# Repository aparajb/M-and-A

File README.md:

# M&amp;A
#### M&amp;A Repository
**The Team:** Aparaj Bogahawatta, Matthew Feros, Gus Gannon
---------------------------------------------------------------------------------
**We are an Australian lightweight soccer team, competing in the Robocup Junior Lighweight League, as part of Brisbane Boys' College Robotics.**
For enquiries relating to BBC Robotics please visit:
[Brisbane Boys' College Website](http://www.bbc.qld.edu.au).

Alternatively, please contact the Head of Soccer at BBC: [Steven Lau](mailto:slau2@bbc.qld.edu.au).

For more information about Robocup Australia, please visit: [Robocup Junior Australia](https://www.robocupjunior.org.au/).

For more information about our Robots, please visit our website: [M&amp;A Robotics](https://bbcrobotics-mna.weebly.com).

## Folder Structure
- M&amp;A 2018 : All the designs, electronics and software for our 2018 national robots
    - Hardware : Contains all the structural components and electronic components of our robot
    - Log Book : Contains the manufacturing process of our original robot
    - Management : Contains some files for management
    - Orders : Contains an order spreadsheet which has all our electrical and structural components
    - Software : Contains the software for our microcontrollers
        - lib : Contains libraries of code referred to in the main program
        - src : Contains the source code for the Master Teensy

- M&amp;A 2019 : All the designs, electronics and software for our 2019 international robots
    - Documentation : Contains a handout, presentation and poster for our team.
    - Hardware : Contains all the structural components and electronic components of our robot
    - Orders : Contains an order spreadsheet which has all our electrical and structural components
    - Project Management : Contains our project management plan for the international competition
    - Rules : Contains the international and national rules    
    - Software : Contains the software for our microcontrollers
        - lib : Contains libraries of code referred to in the main program
        - src : Contains the source code for the Master Teensy
        
## Primary Robot Components
- Maxon DCX19s Motors
- Custom Made Omniwheels (3D Print, Laser Cut and CNC)
- Main PCB
    - Teensy 3.5
    - 24 TSSPs
    - IMU (MPU9250)
    - HC-05 Bluetooth Module
    - OpenMV H7
- Light Sensor PCB
    - 32 Light Sensors Arranged in a Circular Formation
- LRF PCB
    - 4 LRFs
- Custom Designed 360° Camera Mirror
## Programming Checklist
- [x] Establish Movement of Motors
- [x] Compass Correction
- [x] Ball Following + Score
- [x] Line Avoidance
- [x] Goal Tracking
- [x] Inter Robot Communication
## 2019 Objectives
#### General Goals
- [x] Increase Attacker accuracy
- [x] Increase Defender accuracy
- [x] Implement Role switching
## Results
#### Brisbane Regional Competition 2018
- 1st Place
#### Queensland State Competition 2018
- 1st Place
#### Australian National Competition Competition 2018
- 2nd Place
#### International Championships 2019
- 1st Place
---------------------------------------------------------------------------------

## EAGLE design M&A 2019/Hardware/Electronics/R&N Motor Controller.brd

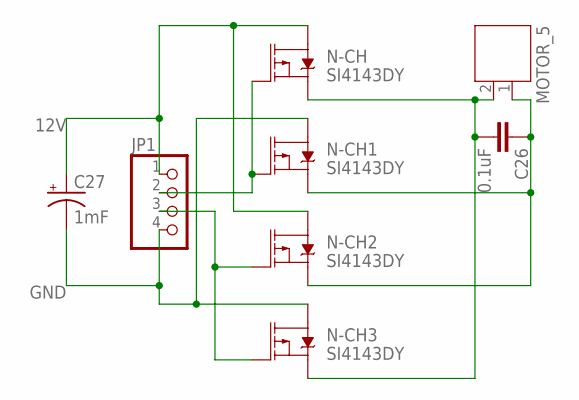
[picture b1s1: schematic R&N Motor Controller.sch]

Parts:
C26: 0.1uF; 0603
C27: 1mF; CPOL-RADIAL-5MM-10MM
JP1: PINHD-1X4; 1X04
MOTOR_5: JST-PH2
N-CH, N-CH1, N-CH2, N-CH3: SI4143DY; SO-8

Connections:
12V: C27.+, JP1.1, N-CH.5 (D), N-CH.6 (D), N-CH.7 (D), N-CH.8 (D), N-CH2.5 (D), N-CH2.6 (D), N-CH2.7 (D), N-CH2.8 (D)
GND: C27.-, JP1.4, N-CH1.5 (D), N-CH1.6 (D), N-CH1.7 (D), N-CH1.8 (D), N-CH3.5 (D), N-CH3.6 (D), N-CH3.7 (D), N-CH3.8 (D)
unnamed: C26.1, MOTOR_5.1, N-CH1.1 (S), N-CH1.2 (S), N-CH1.3 (S), N-CH2.1 (S), N-CH2.2 (S), N-CH2.3 (S)
unnamed: C26.2, MOTOR_5.2, N-CH.1 (S), N-CH.2 (S), N-CH.3 (S), N-CH3.1 (S), N-CH3.2 (S), N-CH3.3 (S)
PWM_INA: JP1.2, N-CH.4 (G), N-CH1.4 (G)
PWM_INB: JP1.3, N-CH2.4 (G), N-CH3.4 (G)

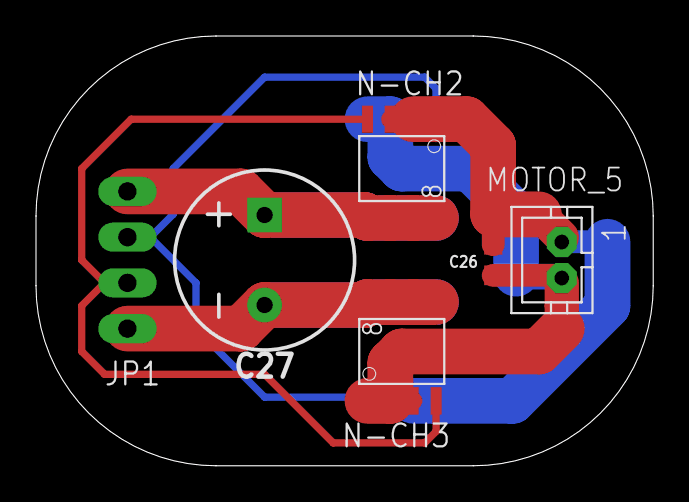
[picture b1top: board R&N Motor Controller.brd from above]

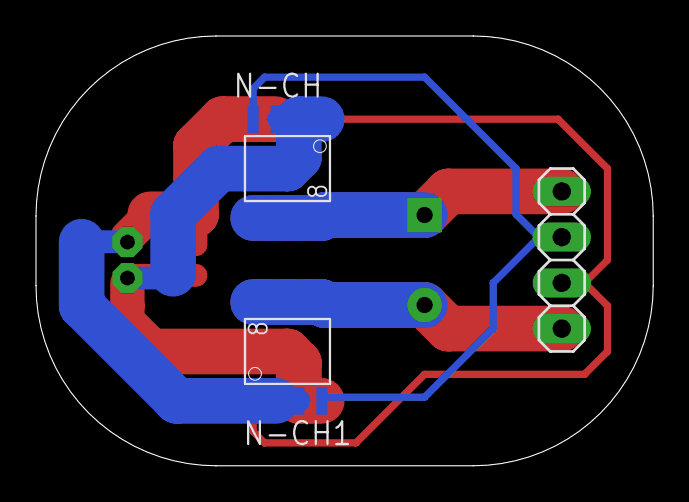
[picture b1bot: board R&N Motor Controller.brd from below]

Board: 2 copper layers, 34.3 x 23.9 mm, 8 parts (3 on the bottom side), 6 nets.

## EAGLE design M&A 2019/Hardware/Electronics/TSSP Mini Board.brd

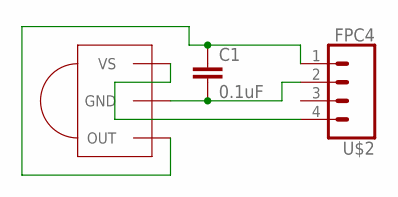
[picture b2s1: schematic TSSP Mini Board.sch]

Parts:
C1: 0.1uF; 0603
U$1: TSSP58038; MINICAST
U$2: FPC4

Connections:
unnamed: C1.1, U$1.1 (OUT), U$2.1
unnamed: C1.2, U$1.2 (GND), U$2.2
unnamed: U$1.3 (VS), U$2.4

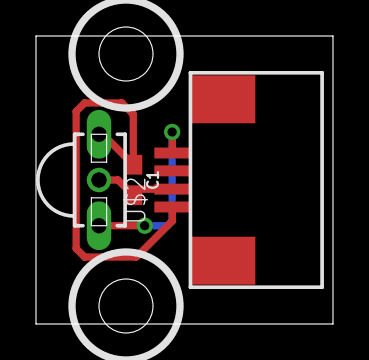
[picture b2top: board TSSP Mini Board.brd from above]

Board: 2 copper layers, 16.5 x 16.0 mm, 3 parts (0 on the bottom side), 3 nets.

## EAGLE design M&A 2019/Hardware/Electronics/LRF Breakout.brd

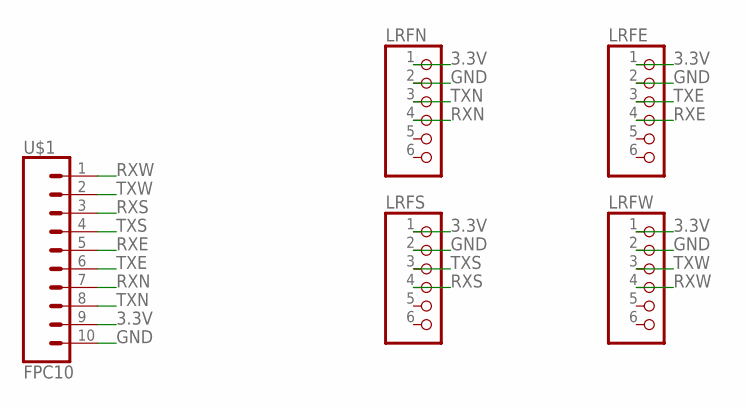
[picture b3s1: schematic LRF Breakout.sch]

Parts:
LRFE: PINHD-1X6; 1X06
LRFN: PINHD-1X6; 1X06
LRFS: PINHD-1X6; 1X06
LRFW: PINHD-1X6; 1X06
U$1: FPC10

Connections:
3.3V: LRFE.1, LRFN.1, LRFS.1, LRFW.1, U$1.9
GND: LRFE.2, LRFN.2, LRFS.2, LRFW.2, U$1.10
RXE: LRFE.4, U$1.5
RXN: LRFN.4, U$1.7
RXS: LRFS.4, U$1.3
RXW: LRFW.4, U$1.1
TXE: LRFE.3, U$1.6
TXN: LRFN.3, U$1.8
TXS: LRFS.3, U$1.4
TXW: LRFW.3, U$1.2

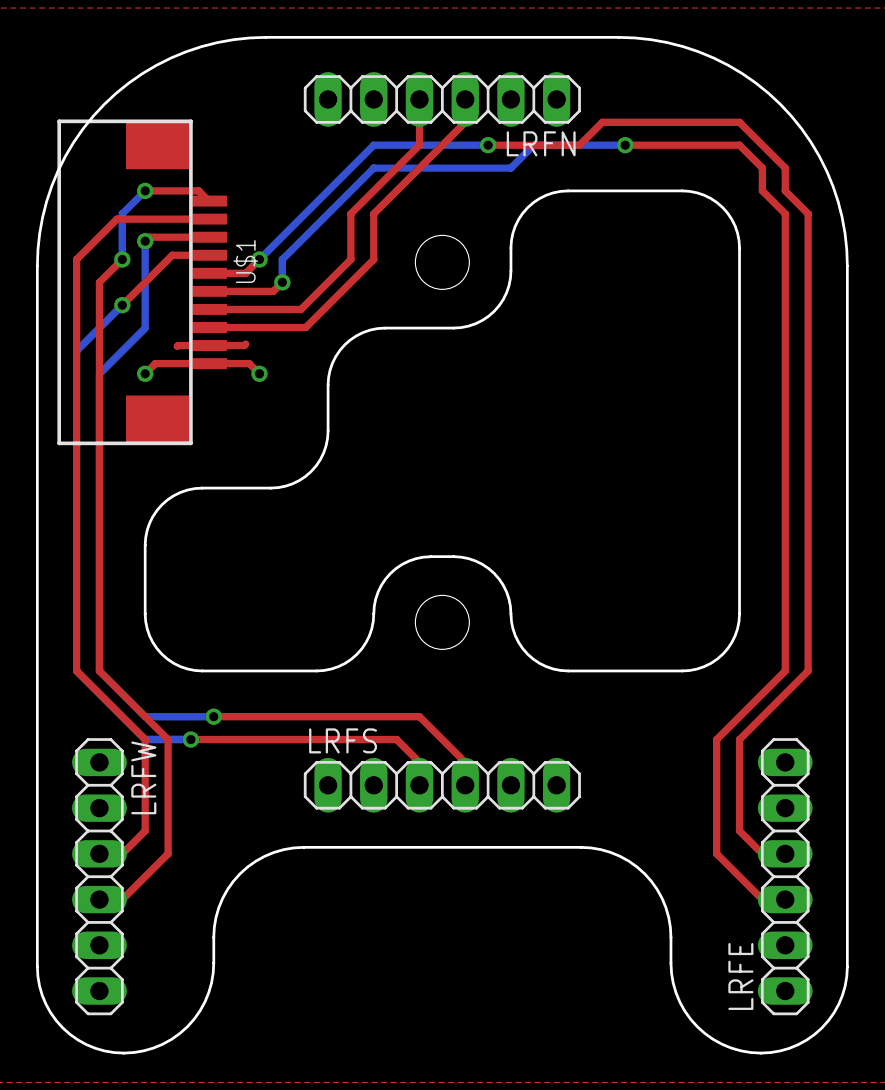
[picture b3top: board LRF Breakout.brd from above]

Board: 2 copper layers, 45.0 x 56.4 mm, 5 parts (0 on the bottom side), 10 nets.

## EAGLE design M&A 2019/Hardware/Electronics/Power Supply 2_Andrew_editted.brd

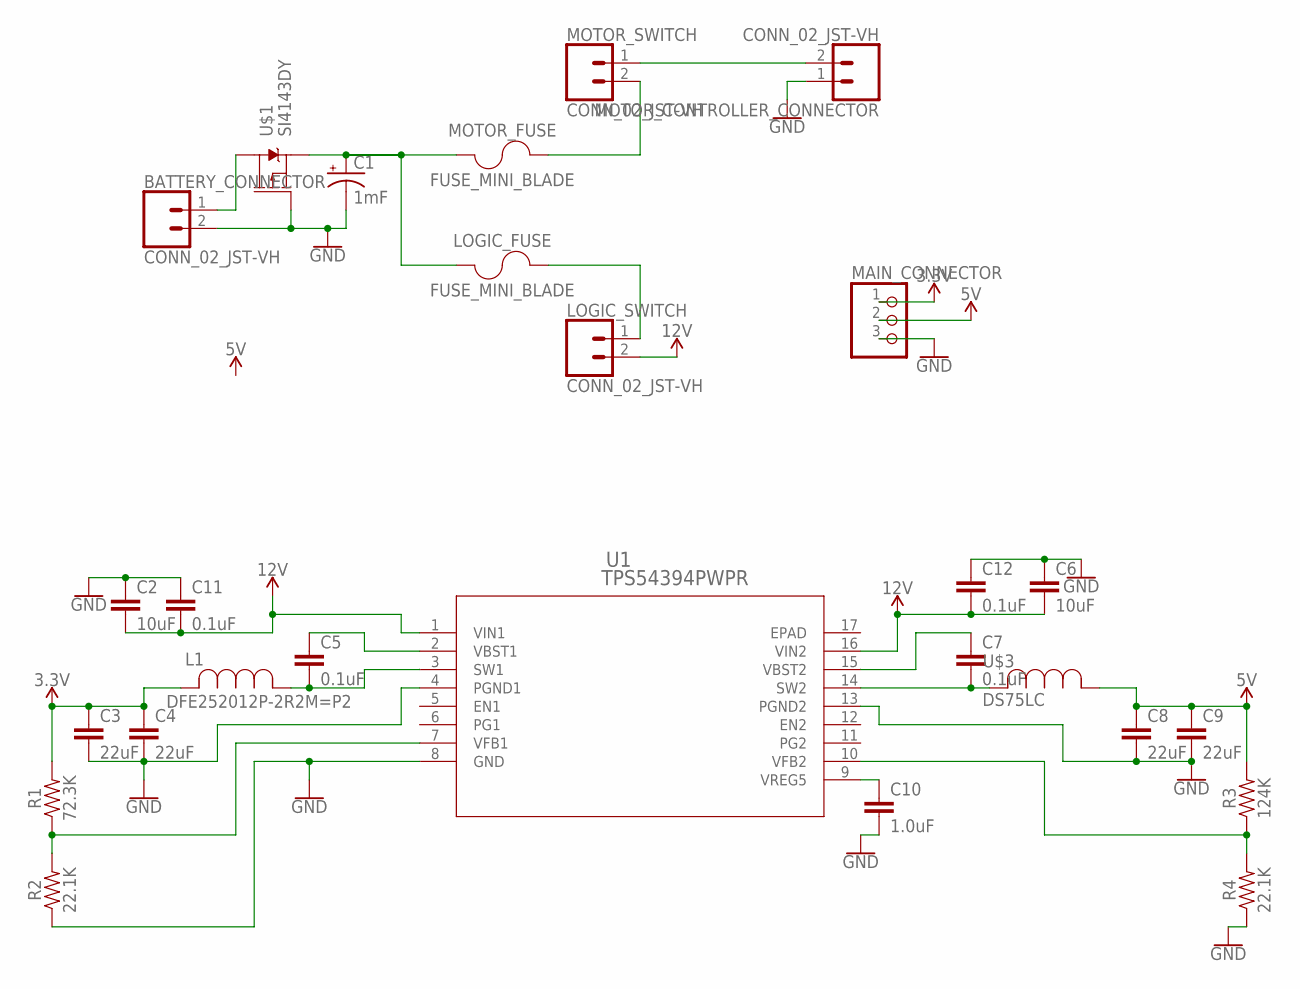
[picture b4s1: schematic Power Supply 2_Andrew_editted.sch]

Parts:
BATTERY_CONNECTOR: CONN_02_JST-VH; B2P-VH
C1: 1mF; CPOL-RADIAL-5MM-10MM
C2, C6: 10uF; 0805
C3, C4, C8, C9: 22uF; 0805
C5, C7, C11, C12: 0.1uF; 0603
C10: 1.0uF; 0805
L1: DFE252012P-2R2M=P2; DFE252012P-1R0M=P2
LOGIC_FUSE: FUSE_MINI_BLADE; SL-1538
LOGIC_SWITCH: CONN_02_JST-VH; B2P-VH
MAIN_CONNECTOR: PINHD-1X3; 1X03
MOTOR_CONTROLLER_CONNECTOR: CONN_02_JST-VH; B2P-VH
MOTOR_FUSE: FUSE_MINI_BLADE; SL-1538
MOTOR_SWITCH: CONN_02_JST-VH; B2P-VH
R1: 72.3K; 0603
R2, R4: 22.1K; 0603
R3: 124K; 0603
U1: TPS54394PWPR; PWP16_3P4X2P46
U$1: SI4143DY; SO-8
U$3: DS75LC

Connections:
3.3V: C3.1, C4.1, L1.2, MAIN_CONNECTOR.1, R1.2
5V: C8.1, C9.1, MAIN_CONNECTOR.2, R3.2, U$3.P$1 (1)
12V: C2.2, C6.2, C11.2, C12.2, LOGIC_SWITCH.2, U1.1 (VIN1), U1.16 (VIN2)
GND: BATTERY_CONNECTOR.2, C1.-, C2.1, C3.2, C4.2, C6.1, C8.2, C9.2, C10.2, C11.1, C12.1, MAIN_CONNECTOR.3, MOTOR_CONTROLLER_CONNECTOR.1, R2.1, R4.1, U1.4 (PGND1), U1.8 (GND), U1.13 (PGND2), U$1.4 (G)
unnamed: BATTERY_CONNECTOR.1, U$1.5 (D), U$1.6 (D), U$1.7 (D), U$1.8 (D)
unnamed: MOTOR_FUSE.P$2 (2), MOTOR_SWITCH.2
unnamed: C1.+, LOGIC_FUSE.P$1 (1), MOTOR_FUSE.P$1 (1), U$1.1 (S), U$1.2 (S), U$1.3 (S)
unnamed: LOGIC_FUSE.P$2 (2), LOGIC_SWITCH.1
unnamed: MOTOR_CONTROLLER_CONNECTOR.2, MOTOR_SWITCH.1
unnamed: C5.1, U1.2 (VBST1)
unnamed: C5.2, L1.1, U1.3 (SW1)
unnamed: C7.1, U1.15 (VBST2)
unnamed: R1.1, R2.2, U1.7 (VFB1)
unnamed: C7.2, U1.14 (SW2), U$3.P$2 (2)
unnamed: C10.1, U1.9 (VREG5)
unnamed: R3.1, R4.2, U1.10 (VFB2)

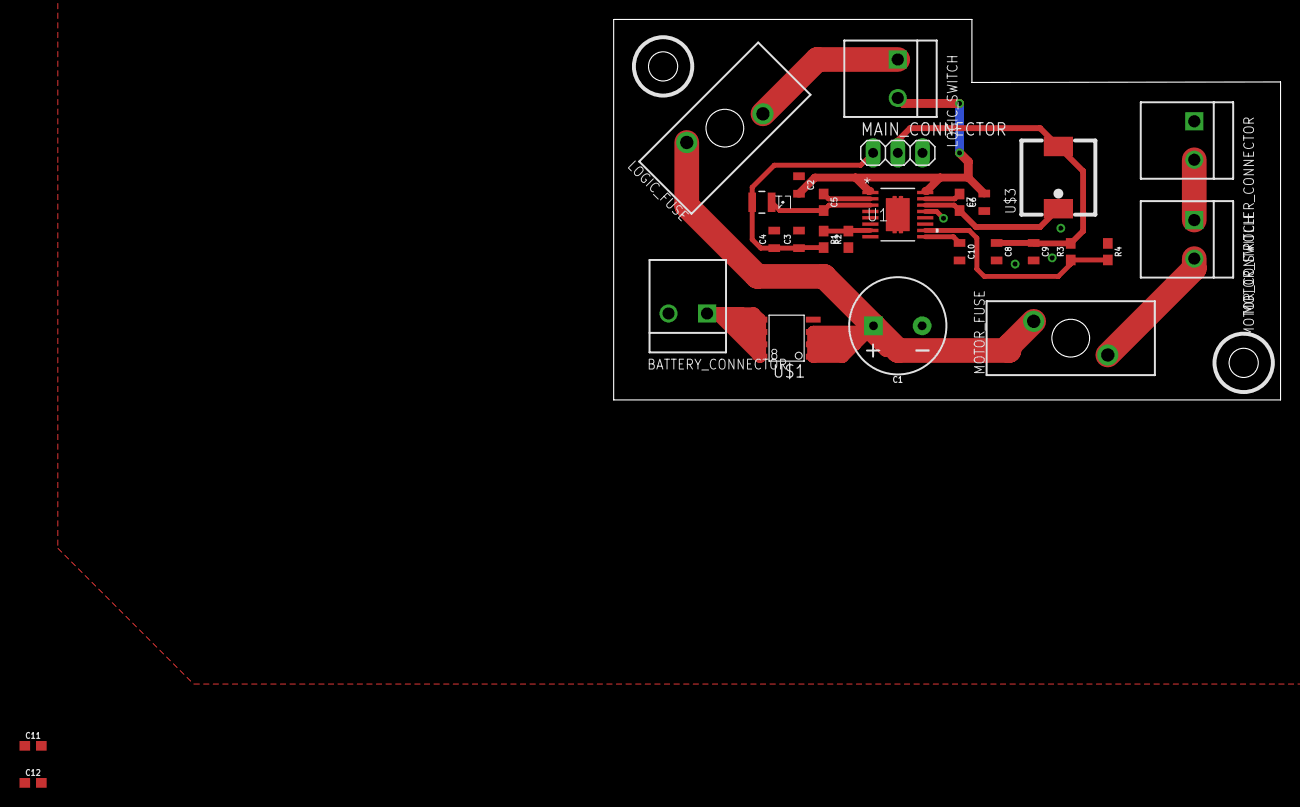
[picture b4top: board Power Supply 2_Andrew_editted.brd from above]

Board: 2 copper layers, 68.6 x 39.1 mm, 27 parts (0 on the bottom side), 16 nets.

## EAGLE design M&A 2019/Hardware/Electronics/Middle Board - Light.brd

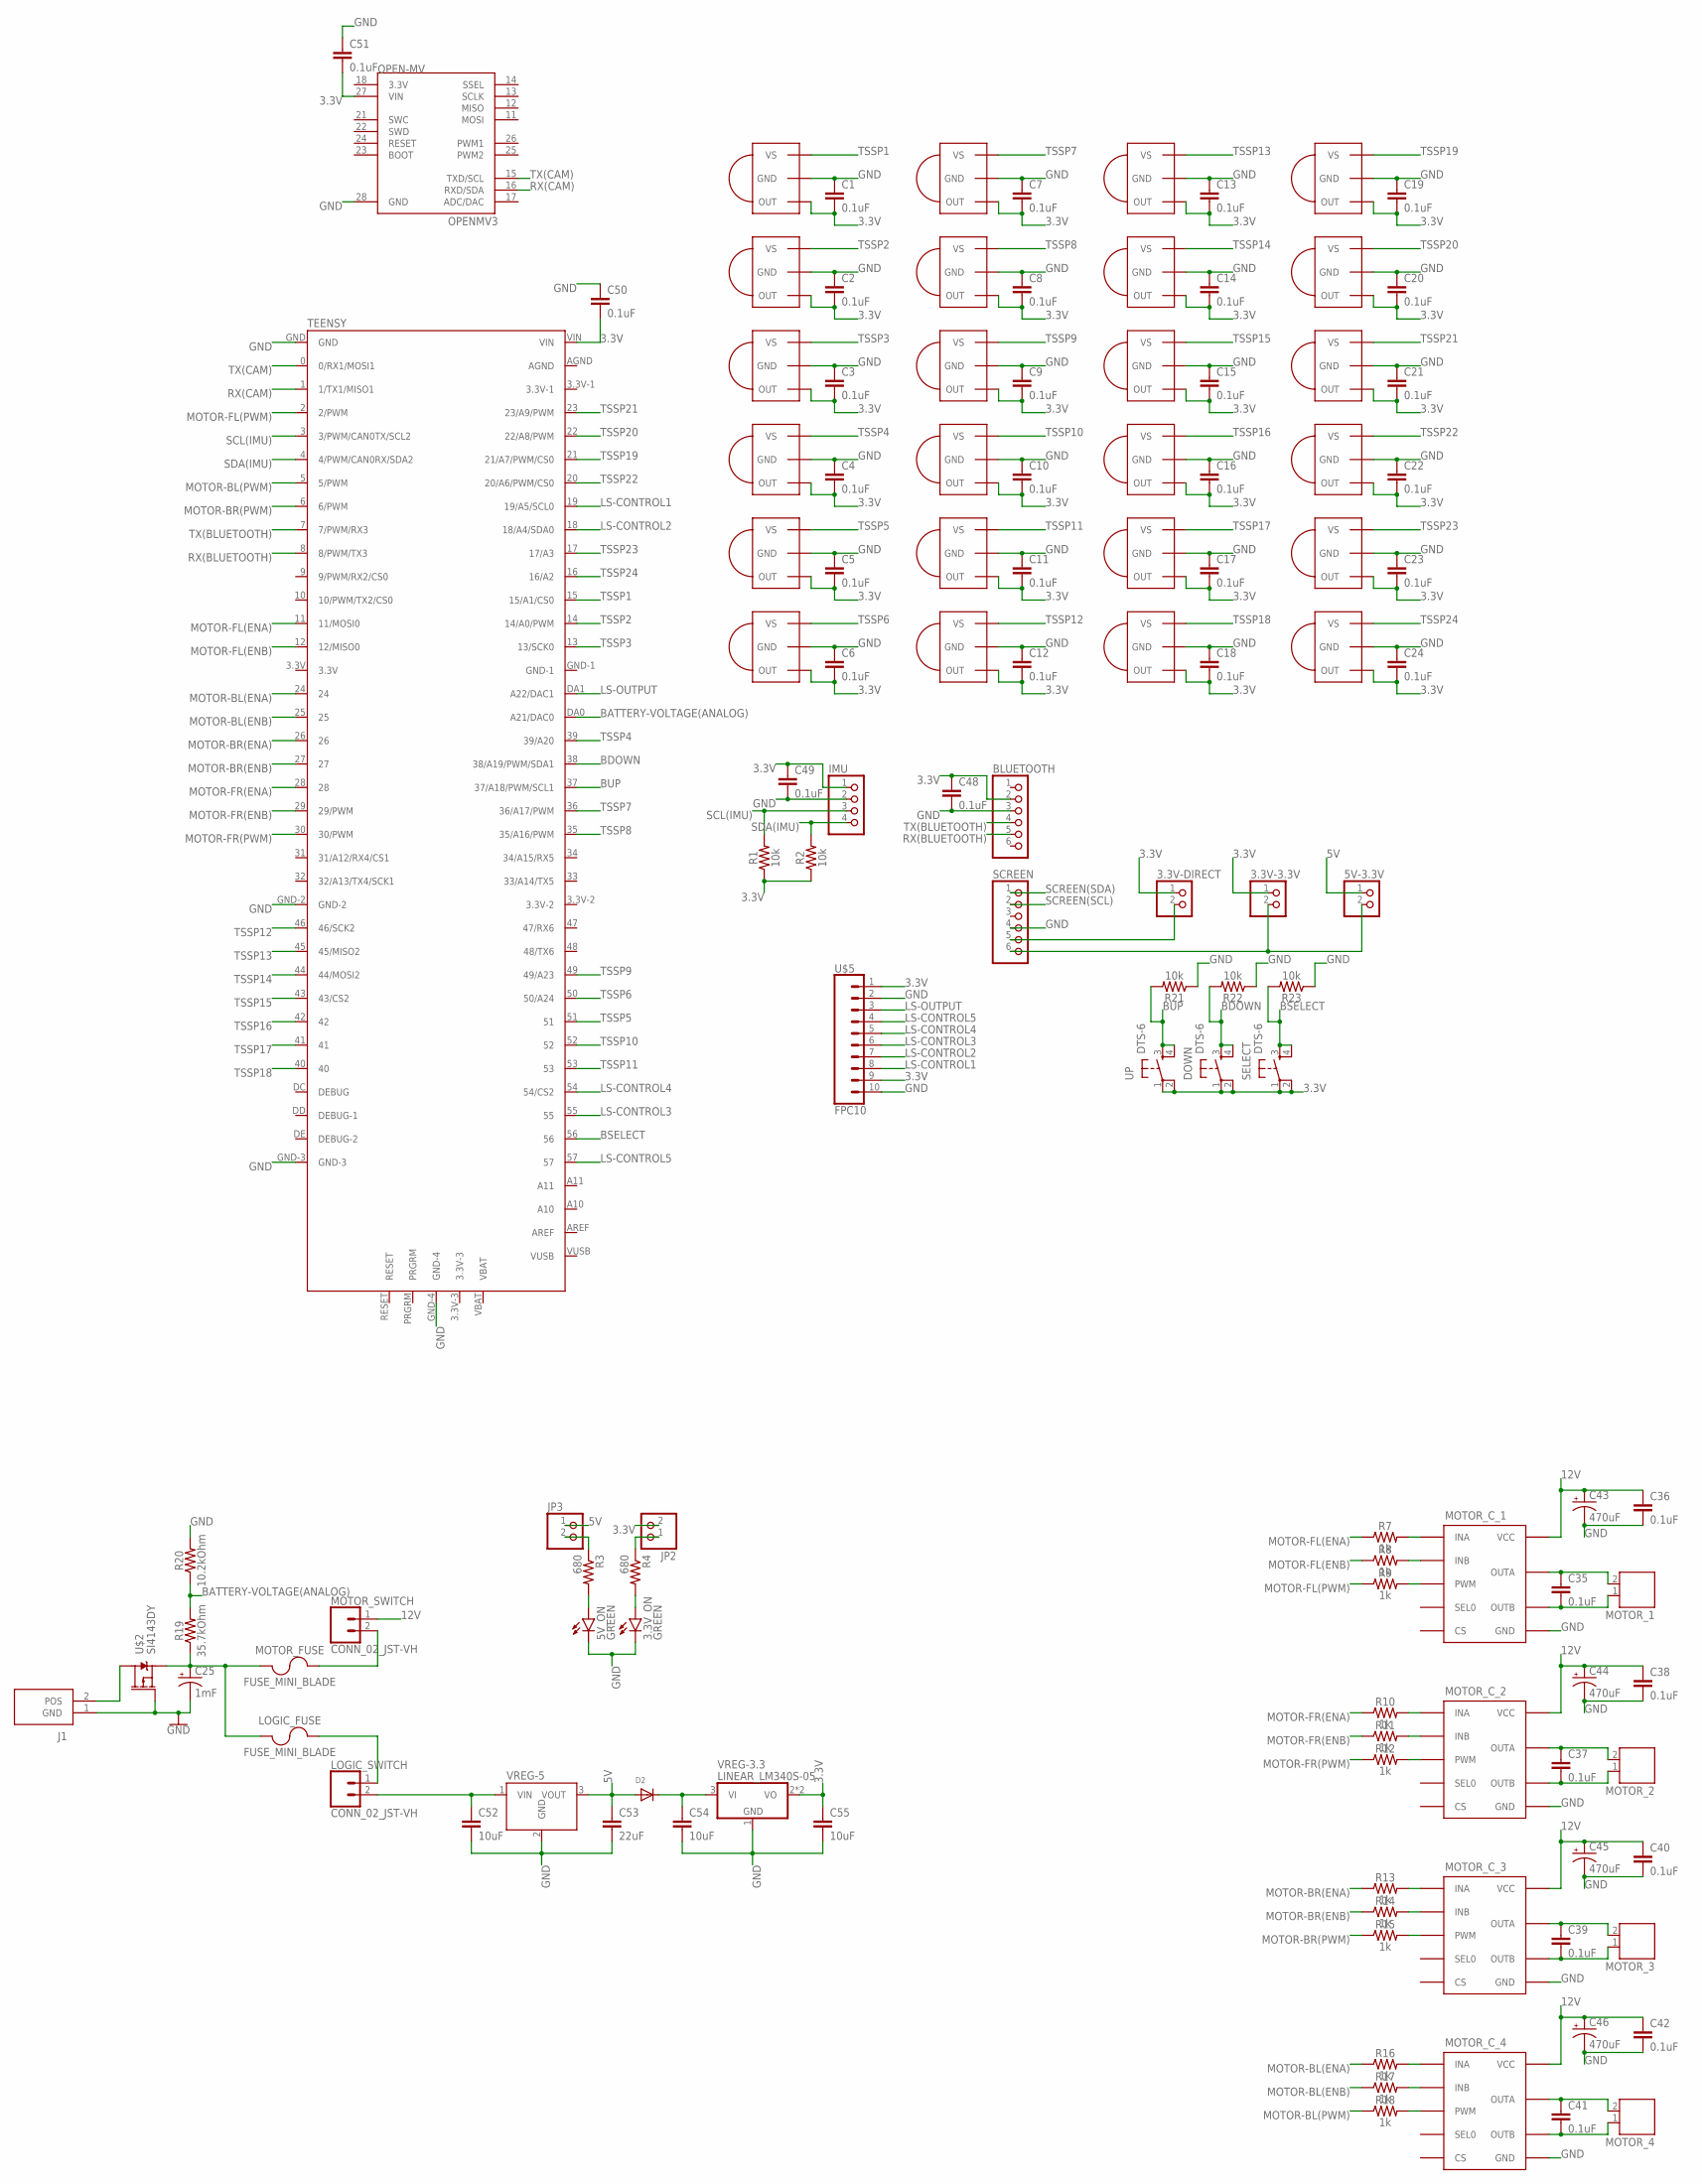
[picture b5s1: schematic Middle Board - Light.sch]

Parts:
3.3V-3.3V, 3.3V-DIRECT, 5V-3.3V: PINHD-1X2; 1X02
3.3V_ON, 5V_ON: GREEN; LED-0603
BLUETOOTH: PINHD-1X6; 1X06
C1, C2, C3, C4, C5, C6, C7, C8, C9, C10, C11, C12, C13, C14, C15, C16, C17, C18, C19, C20, C21, C22, C23, C24, C35, C36, C37, C38, C39, C40, C41, C42, C48, C49, C50, C51: 0.1uF; 0603
C25: 1mF; CPOL-RADIAL-5MM-10MM
C43, C44, C45, C46: 470uF; E3,5-8
C52, C54, C55: 10uF; SPARKFUN-CAPACITORS_0805
C53: 22uF; SPARKFUN-CAPACITORS_1206
D2: ADAFRUIT_DIODE_SOD-123FL:1; ADAFRUIT_SOD-123FL
DOWN: DTS-6
IMU: PINHD-1X4; 1X04
J1: PRT-10474; SHDR2W320P716_1X2_1574X813X158
JP2, JP3: PINHD-1X2/90; 1X02/90
LOGIC_FUSE: FUSE_MINI_BLADE; SL-1538
LOGIC_SWITCH: CONN_02_JST-VH; B2P-VH
MOTOR_1, MOTOR_2, MOTOR_3, MOTOR_4: JST-PH2
MOTOR_C_1, MOTOR_C_2, MOTOR_C_3, MOTOR_C_4: VNH7100BASTR; SO-16
MOTOR_FUSE: FUSE_MINI_BLADE; SL-1538
MOTOR_SWITCH: CONN_02_JST-VH; B2P-VH
OPEN-MV: OPENMV3
R1, R2, R21, R22, R23: 10k; 0603
R3, R4: 680; 0603
R7, R8, R9, R10, R11, R12, R13, R14, R15, R16, R17, R18: 1k; 0603
R19: 35.7kOhm; 0603
R20: 10.2kOhm; 0603
SCREEN: PINHD-1X6; 1X06
SELECT: DTS-6
TEENSY: TEENSY-3.5
TSSP1, TSSP2, TSSP3, TSSP4, TSSP5, TSSP6, TSSP7, TSSP8, TSSP9, TSSP10, TSSP11, TSSP12, TSSP13, TSSP14, TSSP15, TSSP16, TSSP17, TSSP18, TSSP19, TSSP20, TSSP21, TSSP22, TSSP23, TSSP24: TSSP58038; MINICAST
U$2: SI4143DY; SO-8
U$5: FPC10
UP: DTS-6
VREG-3.3: LINEAR_LM340S-05; LINEAR_TO263-3
VREG-5: V78-2000-SWITCHING-REGULATOR_V78-2000

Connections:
3.3V: 3.3V-3.3V.1, 3.3V-DIRECT.1, BLUETOOTH.2, C1.2, C2.2, C3.2, C4.2, C5.2, C6.2, C7.2, C8.2, C9.2, C10.2, C11.2, C12.2, C13.2, C14.2, C15.2, C16.2, C17.2, C18.2, C19.2, C20.2, C21.2, C22.2, C23.2, C24.2, C48.1, C49.1, C50.2, C51.2, C55.1, DOWN.1, DOWN.2, IMU.1, JP2.2, OPEN-MV.27 (VIN), R1.1, R2.1, SELECT.1, SELECT.2, TEENSY.VIN, TSSP1.1 (OUT), TSSP2.1 (OUT), TSSP3.1 (OUT), TSSP4.1 (OUT), TSSP5.1 (OUT), TSSP6.1 (OUT), TSSP7.1 (OUT), TSSP8.1 (OUT), TSSP9.1 (OUT), TSSP10.1 (OUT), TSSP11.1 (OUT), TSSP12.1 (OUT), TSSP13.1 (OUT), TSSP14.1 (OUT), TSSP15.1 (OUT), TSSP16.1 (OUT), TSSP17.1 (OUT), TSSP18.1 (OUT), TSSP19.1 (OUT), TSSP20.1 (OUT), TSSP21.1 (OUT), TSSP22.1 (OUT), TSSP23.1 (OUT), TSSP24.1 (OUT), U$5.1, U$5.9, UP.1, UP.2, VREG-3.3.2 (VO), VREG-3.3.TAB (VO)
3.3V_ON: JP2.1, R4.1
5V: 5V-3.3V.1, C53.1, D2.A, JP3.1, VREG-5.3 (VOUT)
5V-ON: JP3.2, R3.1
12V: C36.1, C38.1, C40.1, C42.1, C43.+, C44.+, C45.+, C46.+, MOTOR_C_1.4 (VCC), MOTOR_C_1.5 (VCC), MOTOR_C_1.12 (VCC), MOTOR_C_2.4 (VCC), MOTOR_C_2.5 (VCC), MOTOR_C_2.12 (VCC), MOTOR_C_3.4 (VCC), MOTOR_C_3.5 (VCC), MOTOR_C_3.12 (VCC), MOTOR_C_4.4 (VCC), MOTOR_C_4.5 (VCC), MOTOR_C_4.12 (VCC), MOTOR_SWITCH.1
BATTERY-VOLTAGE(ANALOG): R19.2, R20.1, TEENSY.DA0 (A21/DAC0)
BDOWN: DOWN.3, DOWN.4, R22.2, TEENSY.38 (38/A19/PWM/SDA1)
BSELECT: R23.2, SELECT.3, SELECT.4, TEENSY.56
BUP: R21.2, TEENSY.37 (37/A18/PWM/SCL1), UP.3, UP.4
GND: 3.3V_ON.C, 5V_ON.C, BLUETOOTH.3, C1.1, C2.1, C3.1, C4.1, C5.1, C6.1, C7.1, C8.1, C9.1, C10.1, C11.1, C12.1, C13.1, C14.1, C15.1, C16.1, C17.1, C18.1, C19.1, C20.1, C21.1, C22.1, C23.1, C24.1, C25.-, C36.2, C38.2, C40.2, C42.2, C43.-, C44.-, C45.-, C46.-, C48.2, C49.2, C50.1, C51.1, C52.2, C53.2, C54.2, C55.2, IMU.2, J1.1 (GND), MOTOR_C_1.1 (GND), MOTOR_C_1.8 (GND), MOTOR_C_1.9 (GND), MOTOR_C_1.16 (GND), MOTOR_C_2.1 (GND), MOTOR_C_2.8 (GND), MOTOR_C_2.9 (GND), MOTOR_C_2.16 (GND), MOTOR_C_3.1 (GND), MOTOR_C_3.8 (GND), MOTOR_C_3.9 (GND), MOTOR_C_3.16 (GND), MOTOR_C_4.1 (GND), MOTOR_C_4.8 (GND), MOTOR_C_4.9 (GND), MOTOR_C_4.16 (GND), OPEN-MV.28 (GND), R20.2, R21.1, R22.1, R23.1, SCREEN.4, TEENSY.GND, TEENSY.GND-2, TEENSY.GND-3, TEENSY.GND-4, TSSP1.2 (GND), TSSP2.2 (GND), TSSP3.2 (GND), TSSP4.2 (GND), TSSP5.2 (GND), TSSP6.2 (GND), TSSP7.2 (GND), TSSP8.2 (GND), TSSP9.2 (GND), TSSP10.2 (GND), TSSP11.2 (GND), TSSP12.2 (GND), TSSP13.2 (GND), TSSP14.2 (GND), TSSP15.2 (GND), TSSP16.2 (GND), TSSP17.2 (GND), TSSP18.2 (GND), TSSP19.2 (GND), TSSP20.2 (GND), TSSP21.2 (GND), TSSP22.2 (GND), TSSP23.2 (GND), TSSP24.2 (GND), U$2.4 (G), U$5.2, U$5.10, VREG-3.3.1 (GND), VREG-5.2 (GND)
LS-CONTROL1: TEENSY.19 (19/A5/SCL0), U$5.8
LS-CONTROL2: TEENSY.18 (18/A4/SDA0), U$5.7
LS-CONTROL3: TEENSY.55, U$5.6
LS-CONTROL4: TEENSY.54 (54/CS2), U$5.5
LS-CONTROL5: TEENSY.57, U$5.4
LS-OUTPUT: TEENSY.DA1 (A22/DAC1), U$5.3
MOTOR-BL(ENA): R16.1, TEENSY.24
MOTOR-BL(ENB): R17.1, TEENSY.25
MOTOR-BL(PWM): R18.1, TEENSY.5 (5/PWM)
MOTOR-BR(ENA): R13.1, TEENSY.26
MOTOR-BR(ENB): R14.1, TEENSY.27
MOTOR-BR(PWM): R15.1, TEENSY.6 (6/PWM)
MOTOR-FL(ENA): R7.1, TEENSY.11 (11/MOSI0)
MOTOR-FL(ENB): R8.1, TEENSY.12 (12/MISO0)
MOTOR-FL(PWM): R9.1, TEENSY.2 (2/PWM)
MOTOR-FR(ENA): R10.1, TEENSY.28
MOTOR-FR(ENB): R11.1, TEENSY.29 (29/PWM)
MOTOR-FR(PWM): R12.1, TEENSY.30 (30/PWM)
unnamed: J1.2 (POS), U$2.5 (D), U$2.6 (D), U$2.7 (D), U$2.8 (D)
unnamed: MOTOR_FUSE.P$2 (2), MOTOR_SWITCH.2
unnamed: C25.+, LOGIC_FUSE.P$1 (1), MOTOR_FUSE.P$1 (1), R19.1, U$2.1 (S), U$2.2 (S), U$2.3 (S)
unnamed: LOGIC_FUSE.P$2 (2), LOGIC_SWITCH.1
unnamed: MOTOR_C_1.3 (INA), R7.2
unnamed: 5V_ON.A, R3.2
unnamed: 3.3V_ON.A, R4.2
unnamed: MOTOR_C_1.6 (INB), R8.2
unnamed: MOTOR_C_1.11 (PWM), R9.2
unnamed: C35.1, MOTOR_1.2, MOTOR_C_1.2 (OUTA), MOTOR_C_1.15 (OUTA)
unnamed: C35.2, MOTOR_1.1, MOTOR_C_1.7 (OUTB), MOTOR_C_1.10 (OUTB)
unnamed: MOTOR_C_2.3 (INA), R10.2
unnamed: MOTOR_C_2.6 (INB), R11.2
unnamed: MOTOR_C_2.11 (PWM), R12.2
unnamed: C37.1, MOTOR_2.2, MOTOR_C_2.2 (OUTA), MOTOR_C_2.15 (OUTA)
unnamed: C37.2, MOTOR_2.1, MOTOR_C_2.7 (OUTB), MOTOR_C_2.10 (OUTB)
unnamed: MOTOR_C_3.3 (INA), R13.2
unnamed: MOTOR_C_3.6 (INB), R14.2
unnamed: MOTOR_C_3.11 (PWM), R15.2
unnamed: C39.1, MOTOR_3.2, MOTOR_C_3.2 (OUTA), MOTOR_C_3.15 (OUTA)
unnamed: C39.2, MOTOR_3.1, MOTOR_C_3.7 (OUTB), MOTOR_C_3.10 (OUTB)
unnamed: MOTOR_C_4.3 (INA), R16.2
unnamed: MOTOR_C_4.6 (INB), R17.2
unnamed: MOTOR_C_4.11 (PWM), R18.2
unnamed: C41.1, MOTOR_4.2, MOTOR_C_4.2 (OUTA), MOTOR_C_4.15 (OUTA)
unnamed: C41.2, MOTOR_4.1, MOTOR_C_4.7 (OUTB), MOTOR_C_4.10 (OUTB)
unnamed: 3.3V-DIRECT.2, SCREEN.5
unnamed: 3.3V-3.3V.2, 5V-3.3V.2, SCREEN.6
unnamed: C52.1, LOGIC_SWITCH.2, VREG-5.1 (VIN)
unnamed: C54.1, D2.C, VREG-3.3.3 (VI)
RX(BLUETOOTH): BLUETOOTH.5, TEENSY.8 (8/PWM/TX3)
RX(CAM): OPEN-MV.16 (RXD/SDA), TEENSY.1 (1/TX1/MISO1)
SCL(IMU): IMU.3, R1.2, TEENSY.3 (3/PWM/CAN0TX/SCL2)
SCREEN(SCL): SCREEN.2
SCREEN(SDA): SCREEN.1
SDA(IMU): IMU.4, R2.2, TEENSY.4 (4/PWM/CAN0RX/SDA2)
TSSP1: TEENSY.15 (15/A1/CS0), TSSP1.3 (VS)
TSSP2: TEENSY.14 (14/A0/PWM), TSSP2.3 (VS)
TSSP3: TEENSY.13 (13/SCK0), TSSP3.3 (VS)
TSSP4: TEENSY.39 (39/A20), TSSP4.3 (VS)
TSSP5: TEENSY.51, TSSP5.3 (VS)
TSSP6: TEENSY.50 (50/A24), TSSP6.3 (VS)
TSSP7: TEENSY.36 (36/A17/PWM), TSSP7.3 (VS)
TSSP8: TEENSY.35 (35/A16/PWM), TSSP8.3 (VS)
TSSP9: TEENSY.49 (49/A23), TSSP9.3 (VS)
TSSP10: TEENSY.52, TSSP10.3 (VS)
TSSP11: TEENSY.53, TSSP11.3 (VS)
TSSP12: TEENSY.46 (46/SCK2), TSSP12.3 (VS)
TSSP13: TEENSY.45 (45/MISO2), TSSP13.3 (VS)
TSSP14: TEENSY.44 (44/MOSI2), TSSP14.3 (VS)
TSSP15: TEENSY.43 (43/CS2), TSSP15.3 (VS)
TSSP16: TEENSY.42, TSSP16.3 (VS)
TSSP17: TEENSY.41, TSSP17.3 (VS)
TSSP18: TEENSY.40, TSSP18.3 (VS)
TSSP19: TEENSY.21 (21/A7/PWM/CS0), TSSP19.3 (VS)
TSSP20: TEENSY.22 (22/A8/PWM), TSSP20.3 (VS)
TSSP21: TEENSY.23 (23/A9/PWM), TSSP21.3 (VS)
TSSP22: TEENSY.20 (20/A6/PWM/CS0), TSSP22.3 (VS)
TSSP23: TEENSY.17 (17/A3), TSSP23.3 (VS)
TSSP24: TEENSY.16 (16/A2), TSSP24.3 (VS)
TX(BLUETOOTH): BLUETOOTH.4, TEENSY.7 (7/PWM/RX3)
TX(CAM): OPEN-MV.15 (TXD/SCL), TEENSY.0 (0/RX1/MOSI1)

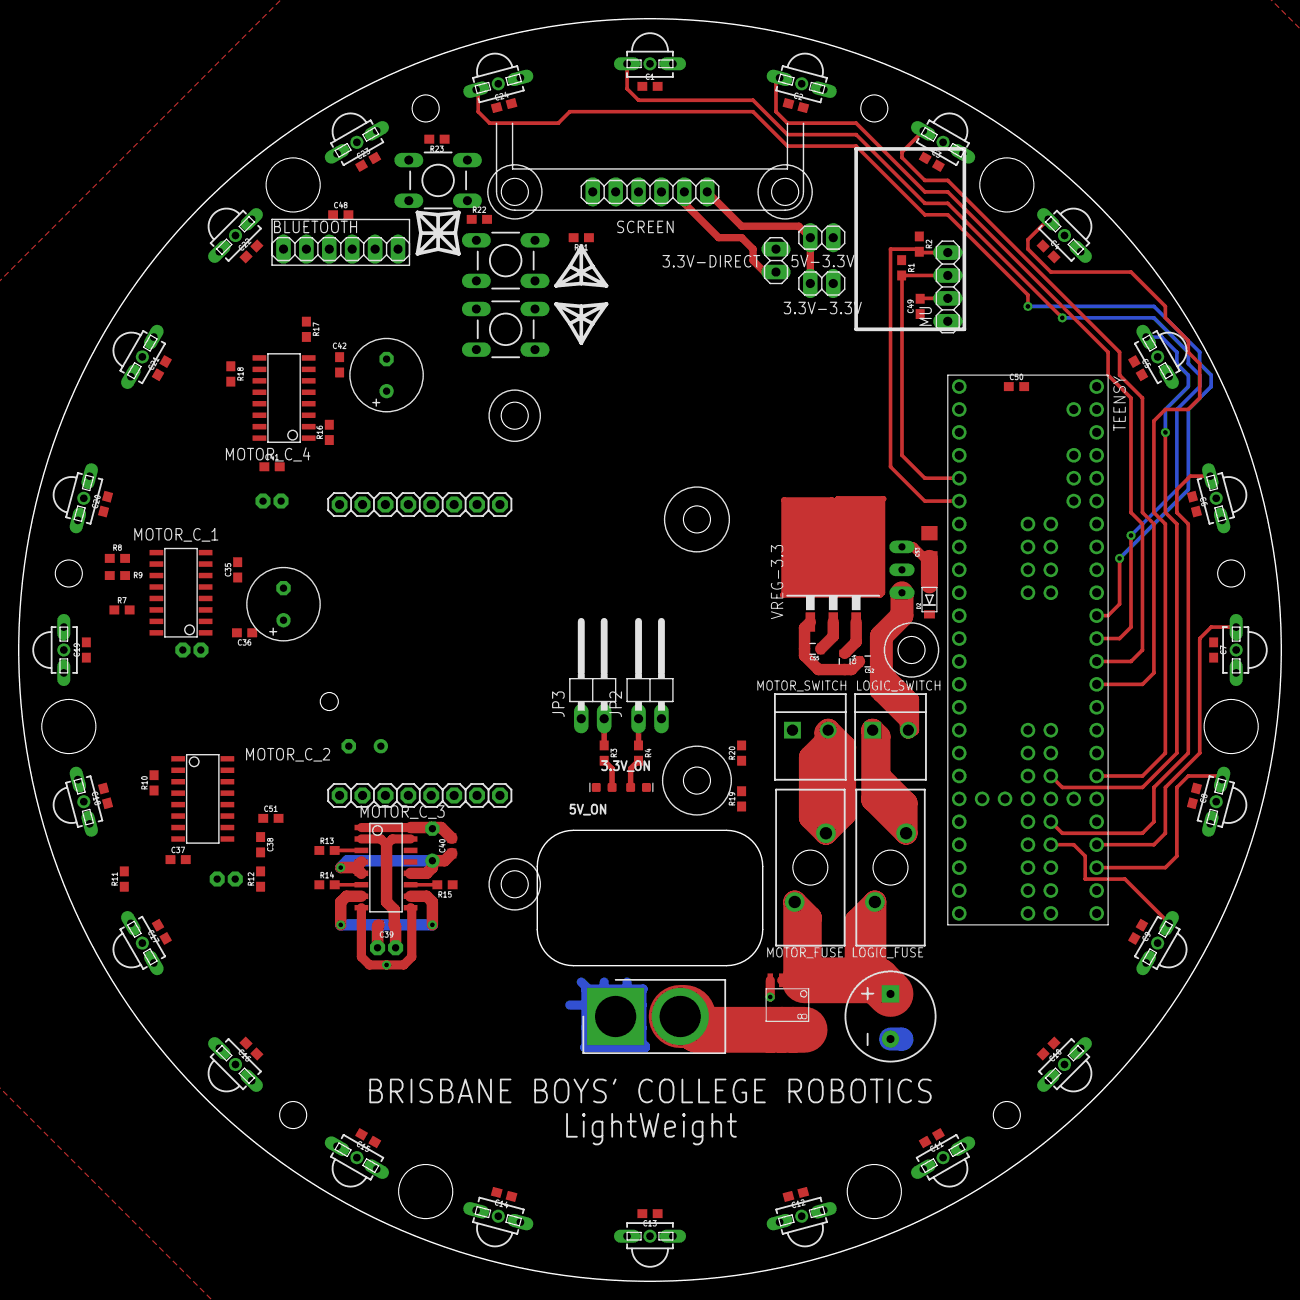
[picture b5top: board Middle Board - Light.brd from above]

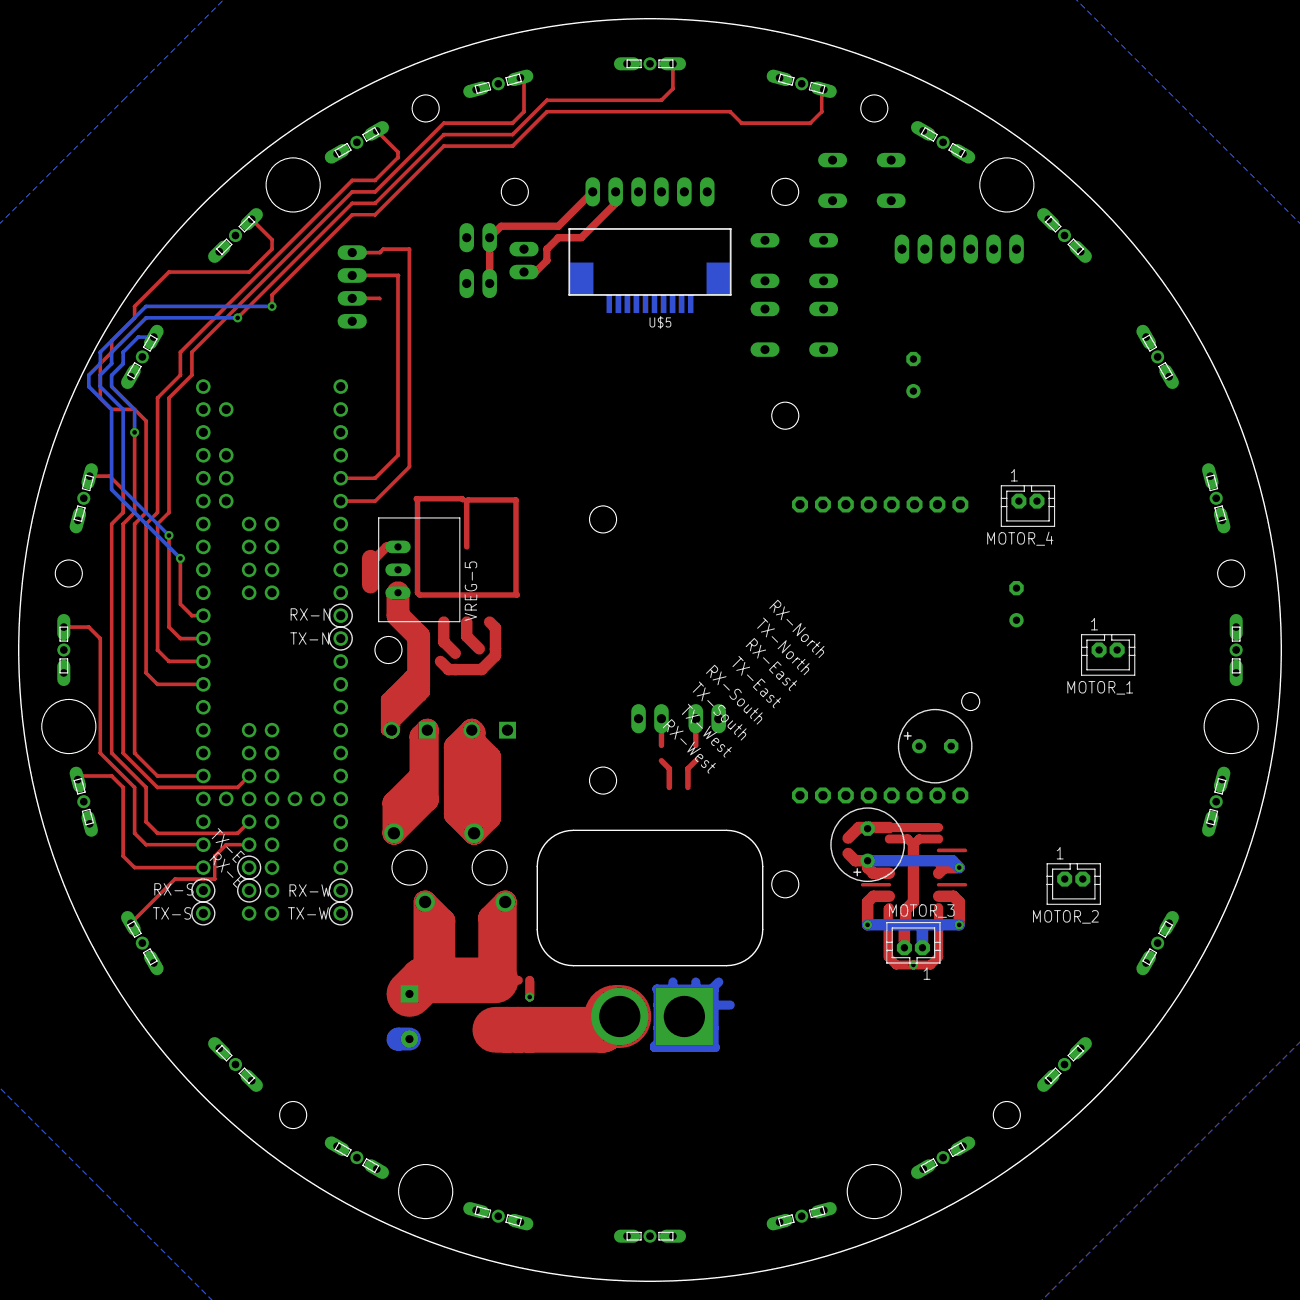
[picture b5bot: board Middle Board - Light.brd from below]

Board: 2 copper layers, 140.0 x 140.0 mm, 123 parts (8 on the bottom side), 88 nets.

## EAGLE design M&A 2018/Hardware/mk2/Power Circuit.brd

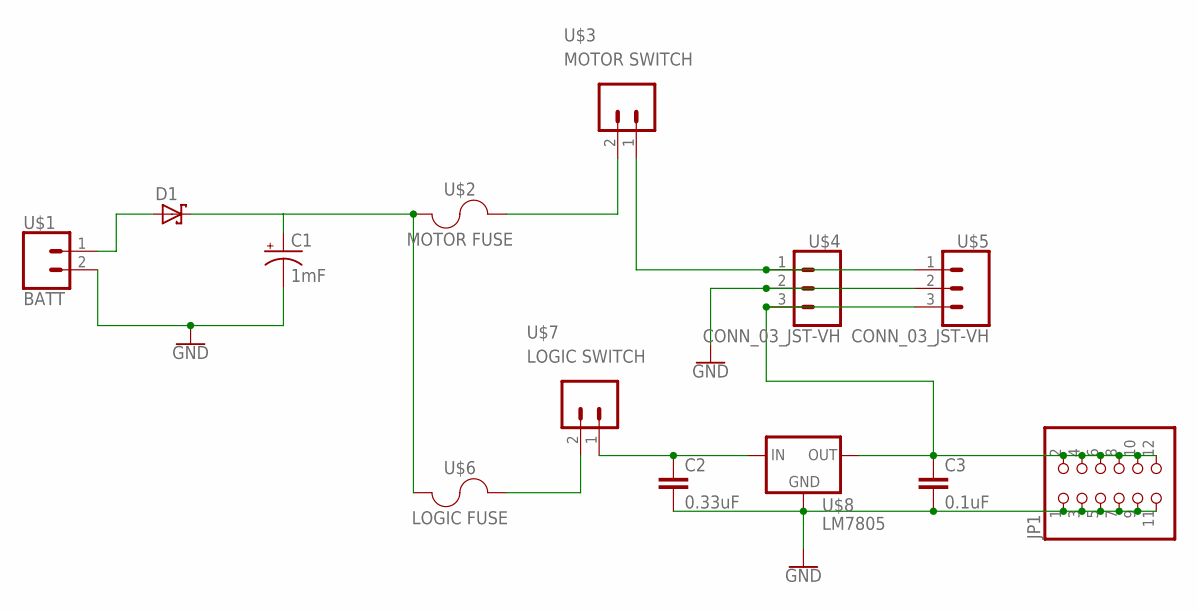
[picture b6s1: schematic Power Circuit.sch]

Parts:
C1: 1mF; CPOL-RADIAL-5MM-10MM
C2: 0.33uF; C5B3
C3: 0.1uF; C5B3
D1: SCHOTTKY-DIODEP6T15; P6T15
JP1: PINHD-2X6; 2X06
U$1: BATT; B2P-VH
U$2: MOTOR FUSE; SL-1538
U$3: MOTOR SWITCH; B2P-VH
U$4, U$5: CONN_03_JST-VH; B3P-VH
U$6: LOGIC FUSE; SL-1538
U$7: LOGIC SWITCH; B2P-VH
U$8: LM7805; TO220-ADJ

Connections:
GND: C1.-, C2.2, C3.2, JP1.1, JP1.3, JP1.5, JP1.7, JP1.9, JP1.11, U$1.2, U$4.2, U$5.2, U$8.GND
unnamed: D1.A, U$1.1
unnamed: C1.+, D1.C, U$2.P$1 (1), U$6.P$1 (1)
unnamed: U$3.1, U$4.1, U$5.1
unnamed: U$2.P$2 (2), U$3.2
unnamed: U$6.P$2 (2), U$7.2
unnamed: C2.1, U$7.1, U$8.INPUT (IN)
unnamed: C3.1, JP1.2, JP1.4, JP1.6, JP1.8, JP1.10, JP1.12, U$4.3, U$5.3, U$8.OUTPUT (OUT)

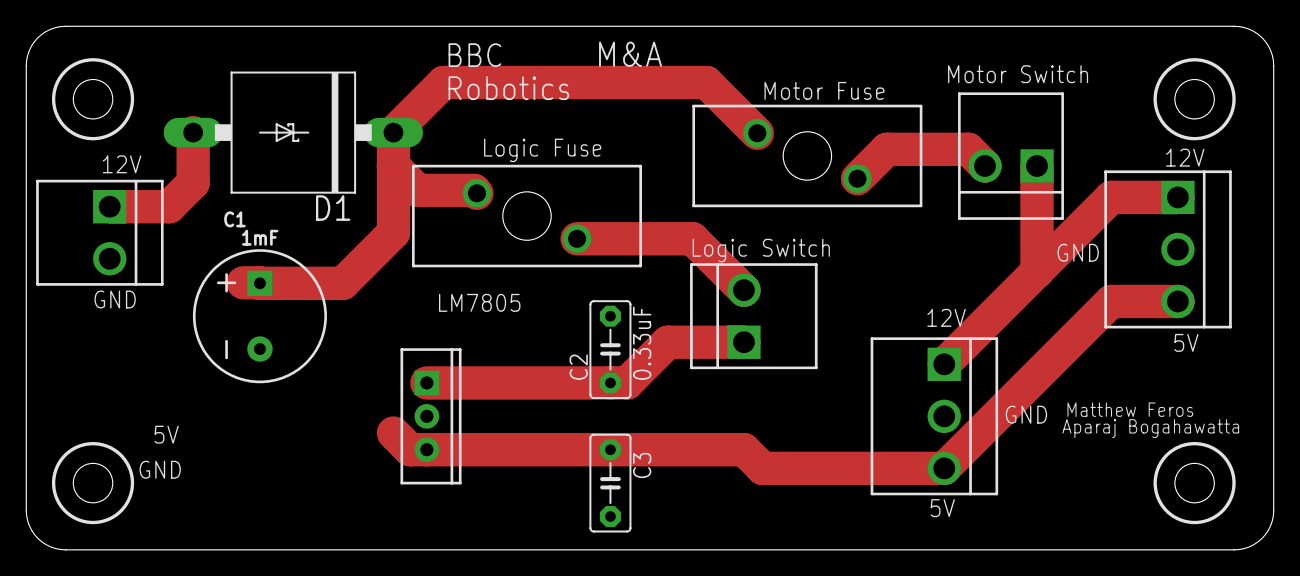
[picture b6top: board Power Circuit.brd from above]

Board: 2 copper layers, 94.9 x 39.8 mm, 12 parts (0 on the bottom side), 8 nets.

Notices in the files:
parts and their libraries:
SparkFun-Resistors: Licensing: Creative Commons ShareAlike 4.0 International - https://creativecommons.org/licenses/by-sa/4.0
